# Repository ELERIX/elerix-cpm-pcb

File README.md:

# CPM PCB

Printed circuit board files

IDE: KiCad

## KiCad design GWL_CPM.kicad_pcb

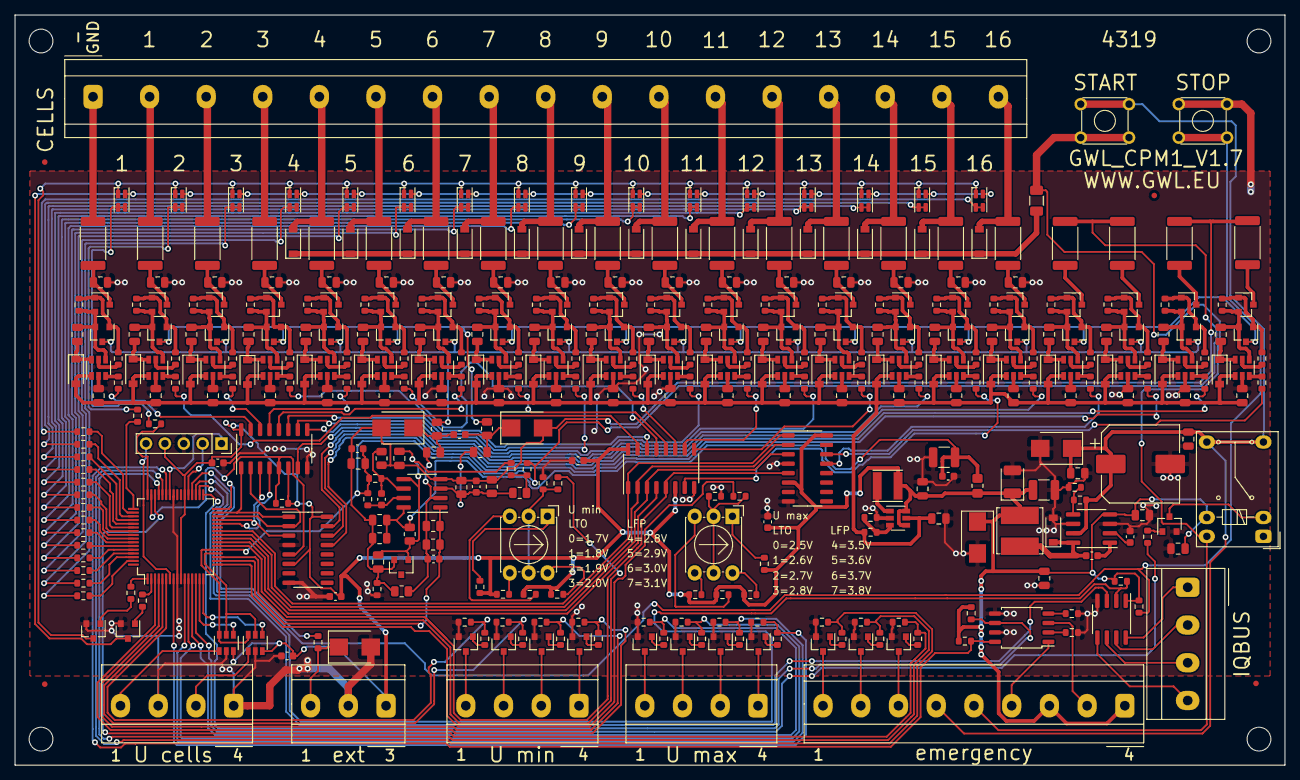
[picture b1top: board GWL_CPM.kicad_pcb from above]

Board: 2 copper layers, 171.0 x 101.0 mm, 425 parts (0 on the bottom side), 309 nets.

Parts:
C301: 47uF/100V - EEEHA2A470UP; CP_Elec_10x10
C302, C303, C304, C311, C314: 10nF/100V X7R 10%; C_0805_2012Metric
C305, C309, C2502, C2507, C2509: 10uF/25V X7R 10%; C_0805_2012Metric
C306, C313, C1501, C1502, C1503, C1504, C1505, C2501: 100nF/25V X7R 10%; C_0603_1608Metric
C307: 100nF/100V X7R 10%; C_0603_1608Metric
C308: 100uF/10V - T495B107M010ATE350; CP_EIA-3528-21_Kemet-B
C310, C312: 22uF/25V X7R 10%; C_1210_3225Metric
C401, C501, C601, C701, C801, C901, C1001, C1101, C1201, C1301, C1401, C1701, C1801, C1901, C2001, C2101, C2201, C2301, C2401, C2701, C2801: 100nF/25V X7R; C_0805_2012Metric
C402, C502, C602, C702, C802, C902, C1002, C1102, C1202, C1302, C1402, C1702, C1802, C1902, C2002, C2102, C2202, C2302, C2402, C2702, C2802: 10uF/25V X7R; C_0805_2012Metric
C403, C503, C603, C703, C803, C903, C1003, C1103, C1203, C1303, C1403, C1703, C1803, C1903, C2003, C2703, C2803: 22nF/250V X7R; C_0805_2012Metric
C2503: 100pF/25V X7R 5%; C_0603_1608Metric
C2504, C2505: 47nF/50V X7R 10%; C_0603_1608Metric
C2506, C2508: 100nF/25V 10% X7R; C_0805_2012Metric
C2510: 33nF/50V 10% X7R; C_0603_1608Metric
D301: SMBJ64; D_SMB
D302: SS110L/BAT46WH; D_SOD-123
D303, D2601: SMBJ5.0; D_SMB
D401, D501, D601, D701, D702, D801, D802, D901, D902, D1001, D1002, D1101, D1102, D1201, D1202, D1301, D1302, D1401, D1402, D1701, D1702, D1801, D1802, D1901, D1902, D2001, D2002, D2101, D2201, D2301, D2401, D2701, D2702, D2801: RR264M-400; D_SOD-123
D1601, D1602, D1603, D1604, D1605, D1606, D1607, D1608, D1609, D1610, D1611, D1612, D1613, D1614, D1615, D1616: KPHBM-2012QBDSURKC
D2501, D2502: SMBJ28; D_SMB
F301: PTC - 60V/100mA; Fuse_1206_3216Metric
FID101, FID102, FID103, FID104: Fiducial; Fiducial_0.75mm_Mask1.5mm
H101: MountingHole1; MountingHole_3.2mm_M3
H102: MountingHole2; MountingHole_3.2mm_M3
H103: MountingHole3; MountingHole_3.2mm_M3
H104: MountingHole4; MountingHole_3.2mm_M3
J1501: SIL05PZ; PinSocket_1x05_P2.54mm_Vertical
J2601: AKZ700; AKZ700_9_5.08
J2602, J2603, J2605, J2607: AKZ700; AKZ700_4_5.08
J2604: AKZ710; AKZ710_17_7.62
J2606: AKZ700; AKZ700_3_5.08
K301: N4100CHS3DC05V; N4100_Relay
L301: 10uH/350mA - FDSD0420-H-100M; L_Taiyo-Yuden_MD-4040
L302: SRN6045TA-221M; L_Bourns_SRN6045TA
L303: MLZ2012N220LT; R_0805_2012Metric_Pad1.20x1.40mm_HandSolder
Q301, Q1601, Q1602, Q2601, Q2602, Q2603, Q2604, Q2605, Q2606, Q2607, Q2608, Q2609, Q2610, Q2611: BC817; SOT-23
Q401, Q402, Q501, Q502, Q601, Q602, Q701, Q702, Q801, Q802, Q901, Q902, Q1001, Q1002, Q1101, Q1102, Q1201, Q1202, Q1301, Q1302, Q1401, Q1402, Q1701, Q1702, Q1801, Q1802, Q1901, Q1902, Q2001, Q2002, Q2101, Q2102, Q2201, Q2202, Q2301, Q2302, Q2401, Q2402, Q2701, Q2702, Q2801, Q2802: BSS131H6327XTSA1; SOT-23
R201: 100k; R_0603_1608Metric
R301, R302, R401, R501, R601, R701, R801, R901, R1001, R1101, R1201, R1301, R1401, R1502, R1601, R1602, R1603, R1604, R1605, R1606, R1607, R1608, R1609, R1610, R1611, R1612, R1613, R1614, R1615, R1616, R1617, R1618, R1701, R1801, R1901, R2001, R2101, R2201, R2301, R2401, R2602, R2605, R2606, R2609, R2610, R2611, R2614, R2615, R2616, R2617, R2618, R2619, R2624, R2625, R2626, R2627, R2701, R2801: 1k; R_0603_1608Metric
R303: 1M; R_0603_1608Metric
R304: 384k; R_0603_1608Metric
R305: 470k; R_0603_1608Metric
R306, R1511, R1512: 33k; R_0603_1608Metric
R307, R2501, R2502, R2503: 0R; R_0603_1608Metric
R402, R502, R602, R702, R802, R902, R1002, R1102, R1202, R1302, R1402, R1505, R1506, R1702, R1802, R1902, R2002, R2102, R2202, R2302, R2402, R2628, R2702, R2802: 100R; R_0603_1608Metric
R403, R503, R603, R703, R803, R903, R1003, R1103, R1203, R1303, R1403, R1703, R1803, R1903, R2003, R2103, R2203, R2303, R2403, R2703, R2803: 22k; R_0603_1608Metric
R404, R504, R604, R704, R804, R904, R1004, R1104, R1204, R1304, R1404, R1704, R1804, R1904, R2004, R2104, R2204, R2304, R2404, R2704: 680R 1W; R_2512_6332Metric
R1501: 2k7; R_0603_1608Metric
R1503, R1504: 3k3; R_0603_1608Metric
R1507, R1508: 6k8; R_0603_1608Metric
R1509, R1510: 15k; R_0603_1608Metric
R2504: 22R; R_0603_1608Metric
R2505, R2506, R2507, R2508: 20k 0.1% 25PPM; R_0805_2012Metric
R2509: 100k 0.1%; R_0805_2012Metric
R2510, R2511: 2k 0.1% 100mW 25PPM; R_0805_2012Metric
R2512, R2513: 10k 0.1% 125mW 25PPM; R_0805_2012Metric
R2514, R2515: 15k 0.1% 250mW 25PPM; R_0805_2012Metric
R2516: 270R; R_0805_2012Metric
R2601, R2603, R2604, R2607, R2608, R2612, R2613, R2620, R2621, R2622, R2623: 10k; R_0603_1608Metric
R2804: 47R 1W; R_2512_6332Metric
SW301, SW302: TC-0104-T; SW_TH_Tactile_Omron_B3F-10xx
SW1501, SW1502: 94HAB08T; Nidec_Copal_SH-7010C
U201, U202, U203, U204: 74HC238; SO-16_3.9x9.9mm_P1.27mm
U301: TLV61046A; SOT-23-6
U302: MAX5033BASA; SOIC-8_3.9x4.9mm_P1.27mm
U401, U501, U601, U701, U801, U901, U1001, U1101, U1201, U1301, U1401, U1701, U1801, U1901, U2001, U2101, U2201, U2301, U2401, U2701, U2801: IRS20752LPBF; SOT-23-6
U1501: PIC16F19196 I/PT; TQFP-64_10x10mm_P0.5mm
U2501: OPA2196xD; SOIC-8_3.9x4.9mm_P1.27mm
U2502: LM4040BIM3-4.1; SOT-23
U2601: ACPL-227-500E; SOIC-8_5.23x5.23mm_P1.27mm
U2603: ISO1540; SOIC-8_3.9x4.9mm_P1.27mm
U2604, U2605: MCP4716; SOT-23-6

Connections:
+5V: C304.1, C305.1, C308.1, C310.1, C311.1, C314.1, C1501.1, C1502.1, C1503.1, C1504.1, C1505.1, D303.1, J1501.4, J2601.1, J2601.3, J2606.1, K301.6, L301.1, L302.2, L303.1, R201.2, R302.2, R1503.1, R1504.1, R1507.1, R1508.1, R1509.1, R1510.1, R1511.1, R1512.1, R2602.1, R2605.1, R2606.1, U201.6, U201.16, U202.6, U202.16, U203.6, U203.16, U204.6, U204.16, U301.4, U301.6, U302.4, U1501.10, U1501.38, U2603.1, U2604.3, U2605.3
+5VA: C312.1, C313.1, C2506.1, C2507.1, L303.2, R2516.2, U2501.8
+12V: C309.1, C401.1, C501.1, C601.1, C701.1, C801.1, C901.1, C1001.1, C1101.1, C1201.1, C1301.1, C1401.1, C1701.1, C1801.1, C1901.1, C2001.1, C2101.1, C2201.1, C2301.1, C2401.1, C2701.1, C2801.1, D401.2, D501.2, D601.2, D701.2, D801.2, D901.2, D1001.2, D1101.2, D1201.2, D1301.2, D1401.2, D1701.2, D1801.2, D1901.2, D2001.2, D2101.2, D2201.2, D2301.2, D2401.2, D2701.2, D2801.2, R305.1, U301.5, U401.1, U501.1, U601.1, U701.1, U801.1, U901.1, U1001.1, U1101.1, U1201.1, U1301.1, U1401.1, U1701.1, U1801.1, U1901.1, U2001.1, U2101.1, U2201.1, U2301.1, U2401.1, U2701.1, U2801.1
/A0: R2801.2, U201.15
/A1: R501.2, U201.14
/A2: R701.2, U201.13
/A3: R901.2, U201.12
/A4: R1101.2, U201.11
/A5: R1301.2, U201.10
/A6: R2001.2, U201.9
/A7: R1801.2, U201.7
/A8: R2701.2, U202.15
/A9: R2401.2, U202.14
/A10: R2201.2, U202.13
/AG: C2501.1, C2502.1, C2504.1, C2506.2, C2507.2, C2508.2, C2509.2, D2501.2, D2502.2, R307.1, R2304.2, R2404.2, R2505.1, R2509.2, R2510.2, R2511.2, U2501.4, U2502.2
/B0: R401.2, U203.15
/B1: R601.2, U203.14
/B2: R801.2, U203.13
/B3: R1001.2, U203.12
/B4: R1201.2, U203.11
/B5: R1401.2, U203.10
/B6: R1901.2, U203.9
/B7: R1701.2, U203.7
/B8: R2301.2, U204.14
/B9: R2101.2, U204.13
/BLUE: R1602.2, U1501.1
/BT_ST_1: C301.1, C302.1, C303.1, D301.1, J2601.6, K301.7, K301.8, R303.2, SW301.1, SW301.2, U302.7
/BT_ST_2: F301.1, J2601.5, K301.14, SW301.3, SW301.4
/C0: J2604.1, R2804.2
/C1: J2604.2, R404.2
/C2: J2604.3, R504.2
/C3: J2604.4, R604.2
/C4: D702.2, J2604.5, R704.2
/C5: D802.2, J2604.6, R804.2
/C6: D902.2, J2604.7, R904.2
/C7: D1002.2, J2604.8, R1004.2
/C8: D1102.2, J2604.9, R1104.2
/C9: D1202.2, J2604.10, R1204.2
/C10: D1302.2, J2604.11, R1304.2
/C11: D1402.2, J2604.12, R1404.2
/C12: D2002.2, J2604.13, R2004.2
/C13: D1902.2, J2604.14, R1904.2
/C14: D1802.2, J2604.15, R1804.2
/C15: D1702.2, J2604.16, R1704.2
/C16: D2702.2, J2604.17, R2704.2
/Differential_Amplifier/VREF1: C2508.1, C2509.1, R2501.1, R2516.1, U2501.5, U2502.1
/EXT: R2628.2, U1501.32
/E_IN_1: R2605.2, U1501.43, U2601.8
/E_IN_2: R2602.2, U1501.33, U2601.6
/E_OC_1: R2601.1, R2609.2, U1501.44
/E_OC_2: R2604.1, R2610.2, U1501.45
/E_OC_3: R2608.1, R2611.2, U1501.46
/IQ_SCL: U1501.34, U2603.3
/IQ_SDA: R2606.2, U1501.35, U2603.2
/LED_C1: R1603.2, U1501.48
/LED_C2: R1605.2, U1501.49
/LED_C3: R1607.2, U1501.63
/LED_C4: R1609.2, U1501.62
/LED_C5: R1611.2, U1501.61
/LED_C6: R1613.2, U1501.60
/LED_C7: R1615.2, U1501.59
/LED_C8: R1617.2, U1501.58
/LED_C9: R1618.2, U1501.57
/LED_C10: R1616.2, U1501.56
/LED_C11: R1614.2, U1501.55
/LED_C12: R1612.2, U1501.54
/LED_C13: R1610.2, U1501.53
/LED_C14: R1608.2, U1501.52
/LED_C15: R1606.2, U1501.51
/LED_C16: R1604.2, U1501.50
/MCU/ICSPCLK: J1501.1, U1501.42
/MCU/ICSPDAT: J1501.2, U1501.37
/MCU/MCLR: J1501.5, U1501.7
/MCU/UMAX: R1505.1, U1501.17
/MCU/UMIN: R1506.1, U1501.19
/OA: Q502.3, Q702.3, Q902.3, Q1102.3, Q1302.3, Q1802.3, Q2002.3, Q2202.3, Q2402.3, Q2702.3, Q2802.3, R2515.2
/OB: Q402.3, Q602.3, Q802.3, Q1002.3, Q1202.3, Q1402.3, Q1702.3, Q1902.3, Q2102.3, Q2302.3, R2514.2
/OUT_A0: U201.1, U202.1, U1501.31
/OUT_A1: U201.2, U202.2, U1501.30
/OUT_A2: U201.3, U202.3, U1501.29
/OUT_A3: U201.4, U1501.28
/OUT_B0: U203.1, U204.1, U1501.26
/OUT_B1: U203.2, U204.2, U1501.25
/OUT_B2: U203.3, U204.3, U1501.24
/OUT_B3: U203.4, U1501.23
/OUT_DIS_A: R201.1, U201.5, U202.5, U1501.47
/OUT_DIS_B: U203.5, U204.5, U1501.22
/RED: R1601.2, U1501.2
/R_ON: R301.2, U1501.14
/SW_STOP: R302.1, SW302.1, SW302.2, U1501.36
/UCELLS_SCL: U1501.20, U2604.5, U2605.5
/UCELLS_SDA_1: U1501.16, U2604.4
/UCELLS_SDA_2: U1501.15, U2605.4
/UMAX_1: R2603.1, R2614.2, U1501.8
/UMAX_2: R2607.1, R2615.2, U1501.11
/UMAX_3: R2612.1, R2616.2, U1501.12
/UMAX_4: R2613.1, R2617.2, U1501.13
/UMIN_1: R2620.1, R2624.2, U1501.3
/UMIN_2: R2621.1, R2625.2, U1501.4
/UMIN_3: R2622.1, R2626.2, U1501.5
/UMIN_4: R2623.1, R2627.2, U1501.6
/VDIFF: C2505.1, R2507.1, R2508.1, U1501.18, U2501.1
/VR2: C2501.2, C2502.2, R2104.2, R2204.2, R2502.1, R2503.1, R2504.1, U1501.21, U2604.6, U2605.6
/VS: D702.1, D802.1, D902.1, D1002.1, D1102.1, D1202.1, D1302.1, D1402.1, D1702.1, D1802.1, D1902.1, D2002.1, D2702.1, F301.2
GND: C301.2, C302.2, C303.2, C304.2, C305.2, C306.2, C308.2, C309.2, C310.2, C311.2, C312.2, C313.2, C314.2, C401.2, C403.2, C501.2, C503.2, C601.2, C603.2, C701.2, C703.2, C801.2, C803.2, C901.2, C903.2, C1001.2, C1003.2, C1101.2, C1103.2, C1201.2, C1203.2, C1301.2, C1303.2, C1401.2, C1403.2, C1501.2, C1502.2, C1503.2, C1504.2, C1505.2, C1701.2, C1703.2, C1801.2, C1803.2, C1901.2, C1903.2, C2001.2, C2003.2, C2101.2, C2201.2, C2301.2, C2401.2, C2701.2, C2703.2, C2801.2, C2803.2, D301.2, D302.2, D303.2, D2601.2, J1501.3, J2605.1, J2605.3, J2606.2, Q301.2, Q1601.2, Q1602.2, Q2601.2, Q2602.2, Q2603.2, Q2604.2, Q2605.2, Q2606.2, Q2607.2, Q2608.2, Q2609.2, Q2610.2, Q2611.2, R304.1, R306.2, R307.2, R1501.2, R1502.2, R2601.2, R2603.2, R2604.2, R2607.2, R2608.2, R2612.2, R2613.2, R2618.2, R2619.2, R2620.2, R2621.2, R2622.2, R2623.2, SW302.3, SW302.4, U201.8, U202.4, U202.8, U203.8, U204.4, U204.8, U301.2, U302.3, U302.6, U401.2, U501.2, U601.2, U701.2, U801.2, U901.2, U1001.2, U1101.2, U1201.2, U1301.2, U1401.2, U1501.9, U1501.41, U1701.2, U1801.2, U1901.2, U2001.2, U2101.2, U2201.2, U2301.2, U2401.2, U2601.5, U2601.7, U2603.4, U2604.2, U2605.2, U2701.2, U2801.2
unnamed: C306.1, U302.2
unnamed: C307.1, D302.1, L302.1, U302.8
unnamed: C307.2, U302.1
unnamed: C402.1, D401.1, U401.6
unnamed: C402.2, Q401.2, Q402.2, R403.1, U401.4
unnamed: C403.1, Q401.3, R404.1
unnamed: C502.1, D501.1, U501.6
unnamed: C502.2, Q501.2, Q502.2, R503.1, U501.4
unnamed: C503.1, Q501.3, R504.1
unnamed: C602.1, D601.1, U601.6
unnamed: C602.2, Q601.2, Q602.2, R603.1, U601.4
unnamed: C603.1, Q601.3, R604.1
unnamed: C702.1, D701.1, U701.6
unnamed: C702.2, Q701.2, Q702.2, R703.1, U701.4
unnamed: C703.1, Q701.3, R704.1
unnamed: C802.1, D801.1, U801.6
unnamed: C802.2, Q801.2, Q802.2, R803.1, U801.4
unnamed: C803.1, Q801.3, R804.1
unnamed: C902.1, D901.1, U901.6
unnamed: C902.2, Q901.2, Q902.2, R903.1, U901.4
unnamed: C903.1, Q901.3, R904.1
unnamed: C1002.1, D1001.1, U1001.6
unnamed: C1002.2, Q1001.2, Q1002.2, R1003.1, U1001.4
unnamed: C1003.1, Q1001.3, R1004.1
unnamed: C1102.1, D1101.1, U1101.6
unnamed: C1102.2, Q1101.2, Q1102.2, R1103.1, U1101.4
unnamed: C1103.1, Q1101.3, R1104.1
unnamed: C1202.1, D1201.1, U1201.6
unnamed: C1202.2, Q1201.2, Q1202.2, R1203.1, U1201.4
unnamed: C1203.1, Q1201.3, R1204.1
unnamed: C1302.1, D1301.1, U1301.6
unnamed: C1302.2, Q1301.2, Q1302.2, R1303.1, U1301.4
unnamed: C1303.1, Q1301.3, R1304.1
unnamed: C1402.1, D1401.1, U1401.6
unnamed: C1402.2, Q1401.2, Q1402.2, R1403.1, U1401.4
unnamed: C1403.1, Q1401.3, R1404.1
unnamed: C1702.1, D1701.1, U1701.6
unnamed: C1702.2, Q1701.2, Q1702.2, R1703.1, U1701.4
unnamed: C1703.1, Q1701.3, R1704.1
unnamed: C1802.1, D1801.1, U1801.6
unnamed: C1802.2, Q1801.2, Q1802.2, R1803.1, U1801.4
unnamed: C1803.1, Q1801.3, R1804.1
unnamed: C1902.1, D1901.1, U1901.6
unnamed: C1902.2, Q1901.2, Q1902.2, R1903.1, U1901.4
unnamed: C1903.1, Q1901.3, R1904.1
unnamed: C2002.1, D2001.1, U2001.6
unnamed: C2002.2, Q2001.2, Q2002.2, R2003.1, U2001.4
unnamed: C2003.1, Q2001.3, R2004.1
unnamed: C2102.1, D2101.1, U2101.6
unnamed: C2102.2, Q2101.2, Q2102.2, R2103.1, U2101.4
unnamed: C2202.1, D2201.1, U2201.6
unnamed: C2202.2, Q2201.2, Q2202.2, R2203.1, U2201.4
unnamed: C2302.1, D2301.1, U2301.6
unnamed: C2302.2, Q2301.2, Q2302.2, R2303.1, U2301.4
unnamed: C2402.1, D2401.1, U2401.6
unnamed: C2402.2, Q2401.2, Q2402.2, R2403.1, U2401.4
unnamed: C2503.1, R2504.2, U2501.7
unnamed: C2503.2, R2503.2, R2509.1, U2501.6
unnamed: C2504.2, R2505.2, R2506.2, R2510.1, R2512.1, U2501.3
unnamed: C2505.2, R2507.2, R2508.2, R2511.1, R2513.1, U2501.2
unnamed: C2510.1, D2502.1, R2513.2, R2515.1
unnamed: C2510.2, D2501.1, R2512.2, R2514.1
unnamed: C2702.1, D2701.1, U2701.6
unnamed: C2702.2, Q2701.2, Q2702.2, R2703.1, U2701.4
unnamed: C2703.1, Q2701.3, R2704.1
unnamed: C2802.1, D2801.1, U2801.6
unnamed: C2802.2, Q2801.2, Q2802.2, R2803.1, U2801.4
unnamed: C2803.1, Q2801.3, R2804.1
unnamed: D1601.1, D1602.1, D1603.1, D1604.1, D1605.1, D1606.1, D1607.1, D1608.1, D1609.1, D1610.1, D1611.1, D1612.1, D1613.1, D1614.1, D1615.1, D1616.1, Q1602.3
unnamed: D1601.2, D1601.3, R1603.1
unnamed: D1601.4, D1602.4, D1603.4, D1604.4, D1605.4, D1606.4, D1607.4, D1608.4, D1609.4, D1610.4, D1611.4, D1612.4, D1613.4, D1614.4, D1615.4, D1616.4, Q1601.3
unnamed: D1602.2, D1602.3, R1604.1
unnamed: D1603.2, D1603.3, R1605.1
unnamed: D1604.2, D1604.3, R1606.1
unnamed: D1605.2, D1605.3, R1607.1
unnamed: D1606.2, D1606.3, R1608.1
unnamed: D1607.2, D1607.3, R1609.1
unnamed: D1608.2, D1608.3, R1610.1
unnamed: D1609.2, D1609.3, R1611.1
unnamed: D1610.2, D1610.3, R1612.1
unnamed: D1611.2, D1611.3, R1613.1
unnamed: D1612.2, D1612.3, R1614.1
unnamed: D1613.2, D1613.3, R1615.1
unnamed: D1614.2, D1614.3, R1616.1
unnamed: D1615.2, D1615.3, R1617.1
unnamed: D1616.2, D1616.3, R1618.1
unnamed: D2601.1, J2606.3, R2628.1
unnamed: J2601.2, U2601.3
unnamed: J2601.4, U2601.1
unnamed: J2601.7, Q2604.3
unnamed: J2601.8, Q2602.3
unnamed: J2601.9, Q2601.3
unnamed: J2602.1, U2603.8
unnamed: J2602.2, U2603.7
unnamed: J2602.3, U2603.6
unnamed: J2602.4, U2603.5
unnamed: J2603.1, Q2603.3
unnamed: J2603.2, Q2605.3
unnamed: J2603.3, Q2606.3
unnamed: J2603.4, Q2607.3
unnamed: J2605.2, U2604.1
unnamed: J2605.4, U2605.1
unnamed: J2607.1, Q2608.3
unnamed: J2607.2, Q2609.3
unnamed: J2607.3, Q2610.3
unnamed: J2607.4, Q2611.3
unnamed: K301.2, Q301.3
unnamed: L301.2, U301.1
unnamed: Q301.1, R301.1
unnamed: Q401.1, Q402.1, R402.1, R403.2
unnamed: Q501.1, Q502.1, R502.1, R503.2
unnamed: Q601.1, Q602.1, R602.1, R603.2
unnamed: Q701.1, Q702.1, R702.1, R703.2
unnamed: Q801.1, Q802.1, R802.1, R803.2
unnamed: Q901.1, Q902.1, R902.1, R903.2
unnamed: Q1001.1, Q1002.1, R1002.1, R1003.2
unnamed: Q1101.1, Q1102.1, R1102.1, R1103.2
unnamed: Q1201.1, Q1202.1, R1202.1, R1203.2
unnamed: Q1301.1, Q1302.1, R1302.1, R1303.2
unnamed: Q1401.1, Q1402.1, R1402.1, R1403.2
unnamed: Q1601.1, R1601.1
unnamed: Q1602.1, R1602.1
unnamed: Q1701.1, Q1702.1, R1702.1, R1703.2
unnamed: Q1801.1, Q1802.1, R1802.1, R1803.2
unnamed: Q1901.1, Q1902.1, R1902.1, R1903.2
unnamed: Q2001.1, Q2002.1, R2002.1, R2003.2
unnamed: Q2101.1, Q2102.1, R2102.1, R2103.2
unnamed: Q2101.3, R2104.1
unnamed: Q2201.1, Q2202.1, R2202.1, R2203.2
unnamed: Q2201.3, R2204.1
unnamed: Q2301.1, Q2302.1, R2302.1, R2303.2
unnamed: Q2301.3, R2304.1
unnamed: Q2401.1, Q2402.1, R2402.1, R2403.2
unnamed: Q2401.3, R2404.1
unnamed: Q2601.1, R2609.1
unnamed: Q2602.1, R2610.1
unnamed: Q2603.1, R2614.1
unnamed: Q2604.1, R2611.1
unnamed: Q2605.1, R2615.1
unnamed: Q2606.1, R2616.1
unnamed: Q2607.1, R2617.1
unnamed: Q2608.1, R2624.1
unnamed: Q2609.1, R2625.1
unnamed: Q2610.1, R2626.1
unnamed: Q2611.1, R2627.1
unnamed: Q2701.1, Q2702.1, R2702.1, R2703.2
unnamed: Q2801.1, Q2802.1, R2802.1, R2803.2
unnamed: R303.1, R304.2, U302.5
unnamed: R305.2, R306.1, U301.3
unnamed: R401.1, U401.3
unnamed: R402.2, U401.5
unnamed: R501.1, U501.3
unnamed: R502.2, U501.5
unnamed: R601.1, U601.3
unnamed: R602.2, U601.5
unnamed: R701.1, U701.3
unnamed: R702.2, U701.5
unnamed: R801.1, U801.3
unnamed: R802.2, U801.5
unnamed: R901.1, U901.3
unnamed: R902.2, U901.5
unnamed: R1001.1, U1001.3
unnamed: R1002.2, U1001.5
unnamed: R1101.1, U1101.3
unnamed: R1102.2, U1101.5
unnamed: R1201.1, U1201.3
unnamed: R1202.2, U1201.5
unnamed: R1301.1, U1301.3
unnamed: R1302.2, U1301.5
unnamed: R1401.1, U1401.3
unnamed: R1402.2, U1401.5
unnamed: R1501.1, R1505.2, SW1501.C
unnamed: R1502.1, R1506.2, SW1502.C
unnamed: R1503.2, SW1501.8
unnamed: R1504.2, SW1502.8
unnamed: R1507.2, SW1501.4
unnamed: R1508.2, SW1502.4
unnamed: R1509.2, SW1501.2
unnamed: R1510.2, SW1502.2
unnamed: R1511.2, SW1501.1
unnamed: R1512.2, SW1502.1
unnamed: R1701.1, U1701.3
unnamed: R1702.2, U1701.5
unnamed: R1801.1, U1801.3
unnamed: R1802.2, U1801.5
unnamed: R1901.1, U1901.3
unnamed: R1902.2, U1901.5
unnamed: R2001.1, U2001.3
unnamed: R2002.2, U2001.5
unnamed: R2101.1, U2101.3
unnamed: R2102.2, U2101.5
unnamed: R2201.1, U2201.3
unnamed: R2202.2, U2201.5
unnamed: R2301.1, U2301.3
unnamed: R2302.2, U2301.5
unnamed: R2401.1, U2401.3
unnamed: R2402.2, U2401.5
unnamed: R2501.2, R2502.2, R2506.1
unnamed: R2618.1, U2601.2
unnamed: R2619.1, U2601.4
unnamed: R2701.1, U2701.3
unnamed: R2702.2, U2701.5
unnamed: R2801.1, U2801.3
unnamed: R2802.2, U2801.5

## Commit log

2021-12-26 ELERIX CPM Full Schematics
